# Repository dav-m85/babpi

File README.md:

# babpi
Follow score and rank players for your football table games, using a [Raspberry Pi](https://www.raspberrypi.org/).

Features:

* Game booking
* Player ranking using XBox's Trueskill algorithm.
* History for all games played
* Simple wiring
* ... or if you want, MSP430 + nrf24l01 transceiver support for wireless with all sources
* Retro look'n'feel

You'll need:

* A Football table
* [Raspberry-pi B+ or later](https://www.raspberrypi.org)
* A screen (to display current game scoreboard)
* Two arcade plunger buttons (to increment score and interact with scoreboard)
* Basic shell understanding
* A few wires

## Installation
### For development
babpi can be run straight from your dev machine with:

    npm install
    npm run dev

Then just open http://127.0.0.1:3000/ in your favorite browser. You can mock the button interface by pressing a, A, b and B.

### Raspberry pi
Follow [this tutorial](https://blog.gordonturner.com/2017/12/10/raspberry-pi-full-screen-browser-raspbian-december-2017/) to get a Pi that starts in kiosk mode (use the following kiosk url ```--kiosk http://127.0.0.1:3000/scoreboard```).

You already have ```git```, ```pip``` ```python``` and ```node``` if you followed the tutorial.

Run the following commands once ssh logged:

    # Latest node version
    curl -sL https://deb.nodesource.com/setup_9.x | sudo -E bash -
    sudo apt install nodejs

    # Setup python for the ranking system
    sudo pip install trueskill

    # We need npm
    sudo apt-get -y install npm

    # Lets put babpi inside the /opt folder
    sudo mkdir /opt/babpi
    sudo chown pi: /opt/babpi
    cd /opt/babpi
    git clone https://github.com/dav-m85/babpi.git .

    # Install dependencies and build the thing
    npm install
    mkdir public
    npm run build

    # Run the server for a test
    node server.js

Opening ```http://ip-of-your-raspberrypi:3000/scoreboard``` should display... the scoreboard.

From here, depending on your hardware setup, you can decide to use one of the following input method:

- **wire**: Pi GPIO is directly connected to the buttons.
- **radio**: A nrf24 remote board is used. You connect a nrf24l01 to the GPIO.

Installation differs for both methods.

#### wire ####
Just wire the buttons straight to the Pi GPIO. By default GPIO17 and 18 are used.

    # We need the on off library
    npm install onoff
    # Lets activate pull ups
    sudo apt-get install device-tree-compiler
    dtc -@ -I dts -O dtb -o mygpio-overlay.dtb hardware/wire/mygpio-overlay.dts
    sudo cp mygpio-overlay.dtb /boot/overlays/mygpio-overlay.dtb
    echo "device_tree_overlay=overlays/mygpio-overlay.dtb" | sudo tree /boot/config.txt
    sudo reboot

Sorry for not giving more info, I don't have many since I'm using the radio myself. I just know it worked at some point.

#### radio ####
A remote radio input is supported with a board running a MSP430G2 and a [nRF24L01](http://www.nordicsemi.com/eng/Products/2.4GHz-RF/nRF24L01).

You'll need to wire appropriately the module:

https://forum.mysensors.org/topic/2437/step-by-step-procedure-to-connect-the-nrf24l01-to-the-gpio-pins-and-use-the-raspberry-as-a-serial-gateway-mysensors-1-x

NRF24L01  Pin	NRF24L01	RPi2	RPi2 – Connector Pin
1	GND	rpi-gnd	(25)
2	VCC	rpi-3v3	(17)
3	CE	rpi-gpio22	(15)
4	CSN	rpi-gpio8	(24)
5	SCK	rpi-sckl	(23)
6	MOSI	rpi-mosi	(19)
7	MISO	rpi-miso	(21)
8	IRQ	rpi-gpio25 (22)

250KBPS

The MSP firmware is available in the [radio folder](./hardware/radio). The Pi installation needs a bit of tweaking:

    npm install nrf

    # edit rc.local
    echo "22" >> /sys/class/gpio/export
    echo "25" >> /sys/class/gpio/export
    ...
    exit 0;

##### Compiling the firmware
There's decent tutorials on TI explaining how to achieve that. For fellow programmers, make sure you [activate HEX output like described here](http://processors.wiki.ti.com/index.php/Generating_and_Loading_MSP430_Binary_Files).

If you are on Mac OS X and uses one of the unsupported launchpad boards (MSP-EXP430G2 like me), you can flash with mspdebug (found in Energia):

    alias mspdebug /Applications/Energia.app/Contents/Java/hardware/tools/msp430/bin/mspdebug
    mspdebug rf2500
    (mspdebug) prog /absolute/path/to/project/firmware.txt

### Misc ###
sudo nano /lib/systemd/system/babpi.service
sudo systemctl enable babpi.service

    [Unit]
    Description=Babpi
    After=network.target

    [Service]
    ExecStart=/usr/bin/node server.js
    WorkingDirectory=/opt/babpi
    StandardOutput=inherit
    StandardError=inherit
    Restart=always
    User=pi

    [Install]
    WantedBy=multi-user.target

sudo nano .config/lxsession/LXDE-pi/autostart

    @lxpanel --profile LXDE-pi
    @pcmanfm --desktop --profile LXDE-pi
    #@xscreensaver -no-splash
    @point-rpi

    # BEGIN ADDED

    # Normal website that does not need any exceptions
    @/usr/bin/chromium-browser --incognito --start-maximized --kiosk http://127.0.0.1/scoreboard
    # Enable mixed http/https content, remember if invalid certs were allowed (ie self signed certs)
    #@/usr/bin/chromium-browser --incognito --start-maximized --kiosk --allow-running-insecure-content --remember-cert-error-dec$
    @unclutter
    @xset s off
    @xset s noblank
    @xset -dpms

    # END ADDED

## TODO
There's still a few things I would like to improve:

* Deal with longClick and shortClick on the GPIO
* Autocomplete player in book page
* Competition mode
* Nicer scoreboard
* Write doc and hardware guide
* long click cancel point instead of canceling game
* long click on both sides cancel the game
* General code cleanup
* Provide graph with player stats, http://nvd3.org/examples/cumulativeLine.html
* End of game, show ranking evolution for players

Feel free to do a Pull Request.

## References
* http://hackaday.com/2015/12/09/embed-with-elliot-debounce-your-noisy-buttons-part-i/ (debouncing them all)
* http://www.moserware.com/2010/03/computing-your-skill.html (amazing resource on trueskill)
* https://davidwalsh.name/street-fighter (the ken used on first page)
* http://www.framboise314.fr/faire-dialoguer-un-raspberry-et-un-arduino-via-nrf24l01/#Installation_de_SPI (wireless inspiration)

## Other projects
* http://blog.makingwaves.com/technology/the-foosball-table-live-status-system/
* http://austin.foos.buzz/about
* https://developer.ibm.com/bluemix/2015/08/06/built-iot-foosball-table-ibm-bluemix/
* https://www.reddit.com/r/AskElectronics/comments/2rqlhy/help_with_building_an_electronic_foosball_scoring/
* http://www.semageek.com/projet-le-robot-champion-de-babyfoot-de-epfl/
* Check [pongdome](https://github.com/busbud/pongdome) it's quite the same thing

## Thanks
- @discreetmayor for the original wireless hardware and firmware design
- @thobardin for his suggestion on Trueskill, first python implementation and continous challenge at the soccer table

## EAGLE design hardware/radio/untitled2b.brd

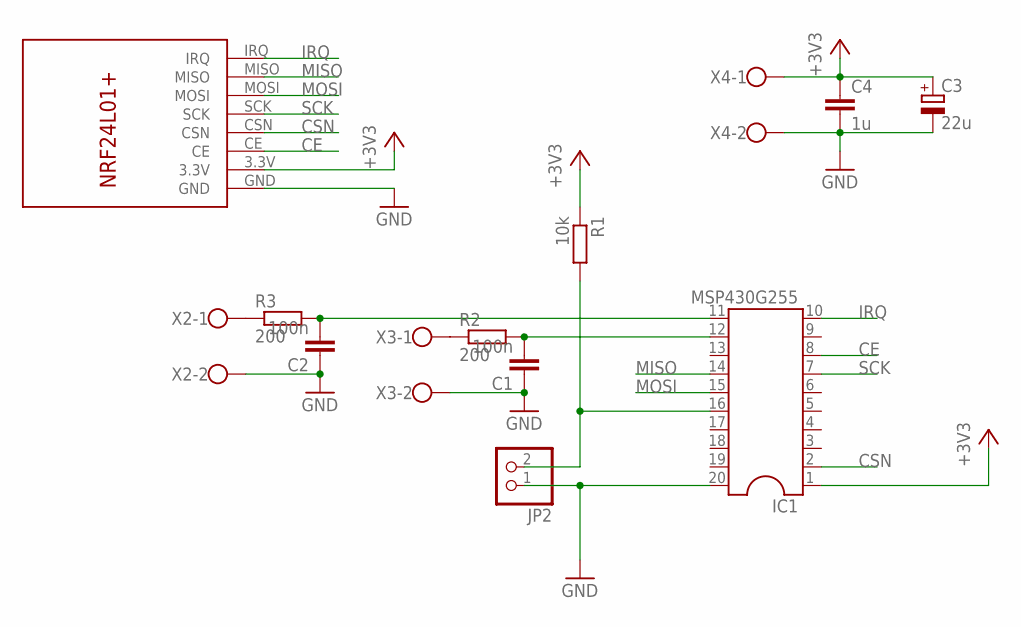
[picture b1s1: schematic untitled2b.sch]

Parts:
C1, C2: 100n; C050-025X075
C3: 22u; E5-8,5
C4: 1u; C050-045X075
IC1: MSP430G255; SOCKET-20
JP2: PINHD-1X2; 1X02
R1: 10k; 0207/10
R2, R3: 200; 0207/10
U$1: NRF24L01
X2, X3, X4: W237-102

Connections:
+3V3: C3.+, C4.1, IC1.1, R1.1, U$1.3.3V, X4.1
CE: IC1.8, U$1.CE
CSN: IC1.2, U$1.CSN
GND: C1.1, C2.1, C3.-, C4.2, IC1.20, JP2.1, U$1.GND, X2.2, X3.2, X4.2
IRQ: IC1.10, U$1.IRQ
MISO: IC1.14, U$1.MISO
MOSI: IC1.15, U$1.MOSI
unnamed: C1.2, IC1.12, R2.2
unnamed: R3.1, X2.1
unnamed: R2.1, X3.1
unnamed: C2.2, IC1.11, R3.2
unnamed: IC1.16, JP2.2, R1.2
SCK: IC1.7, U$1.SCK

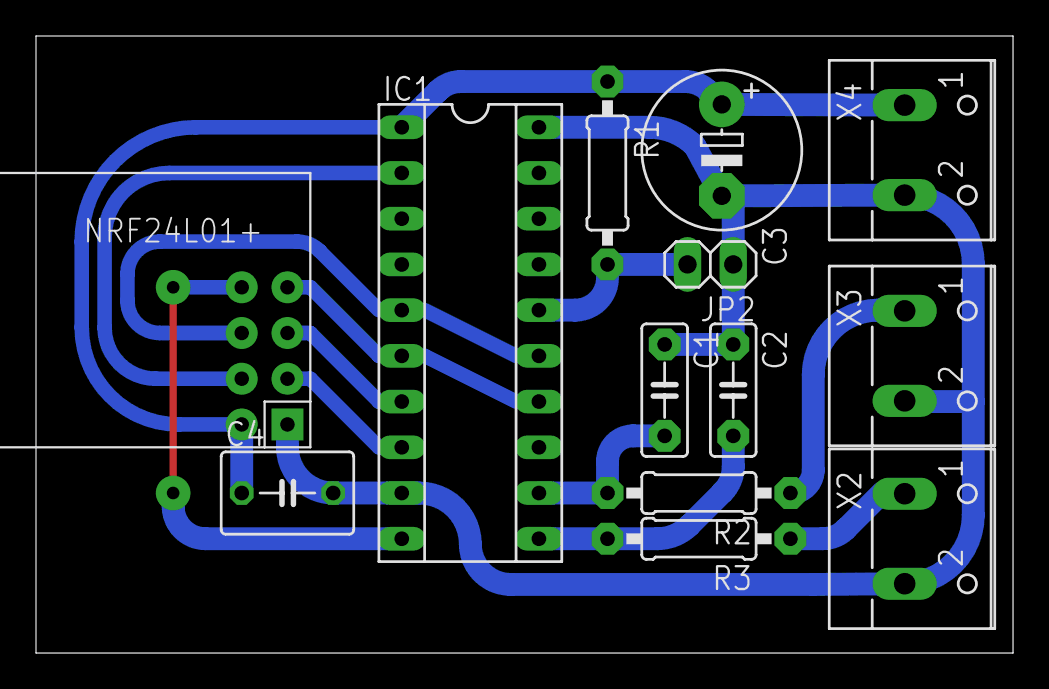
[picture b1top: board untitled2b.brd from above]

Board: 2 copper layers, 54.3 x 34.3 mm, 13 parts (0 on the bottom side), 13 nets.

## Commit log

2016-02-25 first attempts for the screen
2016-03-06 well some skeleton work here
2016-03-06 oyoyo
2016-03-06 build.js should not be in the git
2016-03-06 oops
2016-03-06 adding lowdb
2016-03-06 pomodor night result
2016-03-07 Game logic added
2016-03-07 game mechanics works
2016-03-15 a bit of readme
2016-03-15 fix some bugs and missing libs
2016-03-15 fixing if running from another folder
2016-03-15 GPIO button support
2016-03-15 list a few new toods
2016-03-16 dev instructions
2016-03-16 restructure files
2016-03-17 passing parameters to views at load
2016-03-17 much nicer board, variable game and scoreboard parameter
2016-03-17 even funnier colors
2016-03-17 persist games, history page
2016-03-18 add blue button, Gpio correct path
2016-03-18 storage is absolute now
2016-03-18 bigger fonts
2016-03-18 invert score location on scoreboard
2016-03-21 arch detection, address as a parameter
2016-03-21 fix blink code to be more arcade
2016-03-22 less compilation, views into separate folder
2016-03-23 full less, no precompiled lib, dev works like a charm
2016-03-23 add cyborg less file to play with
2016-03-23 styles are great now
2016-03-23 multi player team support, css sugar
2016-03-24 player leaderboard
2016-03-24 Add rankip_app python API
    Ranking not available yet
2016-03-25 Ranking working
2016-04-01 rematch feature, scoreboard controller is an object now, compute ranking at win
2016-04-01 rank and sugar css
2016-04-01 disable debug for a few commits
2016-04-01 RadioControl
2016-04-05 add ken of sf2 to debug button clicks
2016-04-06 convert ranking app to stdin stdout operation
2016-04-06 working ranking through
2016-04-06 port control from arguments
2016-04-07 ranking implementation
2016-04-07 reverse option
2016-04-07 this I already did
2016-04-07 initd script
2016-04-12 control selection
2016-04-26 more README
2016-12-01 add source files for nrf24l01 module
2016-12-02 README edit
2016-12-02 new code supporting button pushes
2018-01-17 correct button value on send
2018-02-01 button are 1 and 2 in newly created firmware
2018-02-06 switch to webpack 🚀
2018-02-07 clean
2018-02-07 having react for client screens
2018-02-09 working with reducer and ts-trueskill
2018-02-09 reducer tets
2018-02-09 save to db
2018-02-12 player selection first take
2018-02-12 high order component for client socket remote state, with small diff patches
2018-02-13 ui reducer to handle interface changes decoupled from screen skipping logic
2018-02-13 reservation and table selection works like a charm
2018-02-14 red blue colorswap when asked for
2018-02-14 adapting radio control to redux stores
2018-02-14 including built files for faster release on pi
2018-02-14 cleaning
2018-02-16 styling, randomize team color
2018-02-16 debugging tool
2018-02-16 fix archive displays ranking instantaneously on scoreboard
2018-04-06 automatically send long press
